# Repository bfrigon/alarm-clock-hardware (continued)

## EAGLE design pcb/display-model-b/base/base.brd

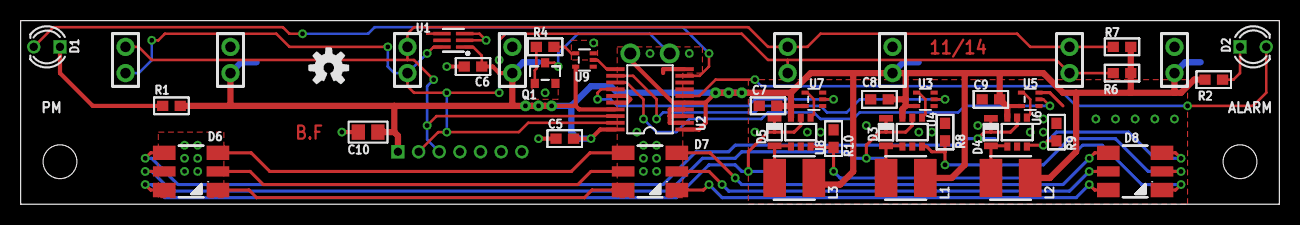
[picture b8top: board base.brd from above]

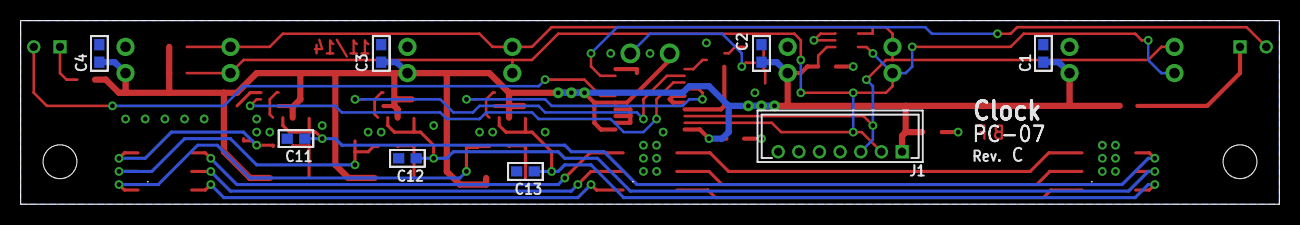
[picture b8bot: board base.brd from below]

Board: 2 copper layers, 121.9 x 17.8 mm, 52 parts (9 on the bottom side), 33 nets.

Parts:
C1, C2, C3, C4, C7, C8, C9, C11, C12, C13: 1uF; SMD_0603
C5, C6: 100nF; SMD_0603
C10: N/A; SMD_0805
D1, D2: {ATTR:COLOR}; LED_3MM
D3, D4, D5: SOD-323
D6, D7, D8: SMP6-RGB; LED_RGB_PLCC6
J1: SNG-2MM-HEADER-07-V; DF3X-7P-2DSA
L1, L2, L3: 22uH; IND-4X4
Q1: MMBT3904; SOT23
R1, R2: 82; SMD_0603
R4: 3k; SMD_0603
R6, R7: 1k; SMD_0603
R8, R9, R10: 5.1 (0.5%); SMD_0603
U1: TSL2561FN; DFN-6
U2: PCA9634PW; TSSOP20
U3, U5, U7, U9: 74AHC1G04DCK; SC70-5
U4, U6, U8: AP5724W; SOT23-6
U$1: INFO_DATE
U$3: OPENHW_LOGO_150
U$4: INFO_COMPACT
U$5: INFO_AUTHOR
X1, X2, X3, X4: CLOCK_LED_SEGMENT
X5: CLOCK_LED_DOTS

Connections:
3.3V: C1.2, C2.2, C3.2, C4.2, C5.1, C6.2, C7.2, C8.2, C9.2, C10.1, J1.1, L1.1, L2.1, L3.1, R1.2, R2.2, R6.2, R7.2, U1.1, U2.1, U2.5, U2.17, U2.20, U3.5, U4.6, U5.5, U6.6, U7.5, U8.6, U9.5, X1.VCC, X2.VCC, X3.VCC, X4.VCC, X5.VCC
DOTS: U2.11, U9.2
FB_B: D8.5, R10.2, U8.3
FB_G: D8.1, R9.2, U6.3
FB_R: D8.3, R8.2, U4.3
GND: C1.1, C2.1, C3.1, C4.1, C5.2, C6.1, C7.1, C8.1, C9.1, C10.2, C11.2, C12.2, C13.2, J1.4, Q1.2, R8.1, R9.1, R10.1, U1.2, U1.3, U2.2, U2.3, U2.4, U2.10, U2.15, U2.16, U3.3, U4.2, U5.3, U6.2, U7.3, U8.2, U9.3, X1.VSS, X2.VSS, X3.VSS, X4.VSS
unnamed: D6.3, D7.4
unnamed: D7.3, D8.4
unnamed: D7.1, D8.2
unnamed: D6.1, D7.2
unnamed: D6.5, D7.6
unnamed: D7.5, D8.6
unnamed: D3.A, L1.2, U4.1
unnamed: D4.A, L2.2, U6.1
unnamed: D5.A, L3.2, U8.1
unnamed: Q1.3, X5.VSS
unnamed: Q1.1, R4.2
unnamed: D2.K, U2.6
unnamed: D2.A, R2.1
unnamed: D1.A, R1.1
unnamed: D1.K, U2.9
unnamed: U3.4, U4.4
unnamed: R4.1, U9.4
unnamed: U5.4, U6.4
unnamed: U7.4, U8.4
PWM_B: U2.14, U7.2
PWM_G: U2.13, U5.2
PWM_R: U2.12, U3.2
SCL: J1.3, R7.1, U1.4, U2.18, X1.SCL, X2.SCL, X3.SCL, X4.SCL
SDA: J1.2, R6.1, U1.6, U2.19, X1.SDA, X2.SDA, X3.SDA, X4.SDA
SW_B: C13.1, D5.K, D6.6, U8.5
SW_G: C11.1, D4.K, D6.2, U6.5
SW_R: C12.1, D3.K, D6.4, U4.5

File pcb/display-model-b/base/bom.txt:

**********************************************************************************
*                                BILL OF MATERIAL                                *
**********************************************************************************

Last mod. : 2014-12-29 01:41:54
Doc. ID   : CLK-SCH-07
Project   : Alarm Clock (Model B)
Title     : Clock Display - Base
             
Part #    : CLK-PC-07
REV.      : C


Qty | Names              | Description                    | Mfg. SKU        | Package      | Value     
=======================================================================================================
  4 | U3, U5, U7, U9     | NOT Gate - Single              | 74AHC1G04DCK    | SC70-5       | --        
----|--------------------|--------------------------------|-----------------|--------------|-----------
  3 | U4, U6, U8         | White LED Step-up converter    | AP5724W         | SOT23-6      | --        
----|--------------------|--------------------------------|-----------------|--------------|-----------
  3 | D3-D5              | Schottky Diode - SMT 0603 -    | B0540WS         | SOD-323      | --        
----|--------------------|--------------------------------|-----------------|--------------|-----------
  2 | C5-C6              | Capacitor - SMT 0603 - 100nF   | CAP-0603        | SMT 0603     | 100nF     
----|--------------------|--------------------------------|-----------------|--------------|-----------
 10 | C1-C4, C7-C9,      | Capacitor - SMT 0603 - 1uF     | CAP-0603        | SMT 0603     | 1uF       
    | C11-C13            |                                |                 |              |           
----|--------------------|--------------------------------|-----------------|--------------|-----------
  1 | J1                 | 2mm Single Row Header - 7 pos  | DF3A-7P-2DSA    | DF3X-7P-2DSA | --        
    |                    | - SMT Vertical                 |                 |              |           
----|--------------------|--------------------------------|-----------------|--------------|-----------
  2 | D1-D2              | Led T1 (3mm) - Green           | LED-T1          | T1           | Green     
----|--------------------|--------------------------------|-----------------|--------------|-----------
  1 | Q1                 | NPN Transistor                 | MMBT3904        | SOT23        | --        
----|--------------------|--------------------------------|-----------------|--------------|-----------
  3 | L1-L3              | Inductor                       | NR4012T220M     | IND-4X4      | 22uH      
----|--------------------|--------------------------------|-----------------|--------------|-----------
  1 | U2                 | 8-bit fm+ i2c-bus LED driver   | PCA9634PW       | TSSOP20      | --        
----|--------------------|--------------------------------|-----------------|--------------|-----------
  2 | R6-R7              | Resistor - SMT 0603 - 1k       | RES-0603        | SMT 0603     | 1k        
----|--------------------|--------------------------------|-----------------|--------------|-----------
  1 | R4                 | Resistor - SMT 0603 - 3k       | RES-0603        | SMT 0603     | 3k        
----|--------------------|--------------------------------|-----------------|--------------|-----------
  3 | R8-R10             | Resistor - SMT 0603 - 5.1      | RES-0603        | SMT 0603     | 5.1       
    |                    | (0.5%)                         |                 |              | (0.5%)    
----|--------------------|--------------------------------|-----------------|--------------|-----------
  2 | R1-R2              | Resistor - SMT 0603 - 82       | RES-0603        | SMT 0603     | 82        
----|--------------------|--------------------------------|-----------------|--------------|-----------
  3 | D6-D8              | SMT RGB Led - PLCC6            | SMP6-RGB        | LED_RGB_PLCC | --        
    |                    |                                |                 | 6            |           
----|--------------------|--------------------------------|-----------------|--------------|-----------
  1 | U1                 | Light-to-digital converter     | TSL2561FN       | DFN-6        | --        
----|--------------------|--------------------------------|-----------------|--------------|-----------

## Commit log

2014-09-07 Added decoupling caps
2014-09-09 Cleaned up project tree
2014-09-18 Added Model B drawings
2014-10-19 Corrected drawings of touch panel PCB
2014-10-23 Overlay design
2014-10-28 Changed files for laser cutting to DXF instead of SVG
2014-12-29 Display base pcb (rev C), Touch panel (rev B)
2015-01-04 Changed page format on schematics to US letter (8.5" x 11")
2015-01-04 Moved notes to docs folder
2015-01-05 Updated mechanical drawings for model B
2015-01-06 3D render for model B
2015-01-06 BOM for audio test board
2015-01-07 Updated overlay to reflect the changes on touch pcb (rev B)
2015-01-09 Added marks for cutting
2015-01-09 Updated drawings to reflect changes on touch keypad PCB (leds on snooze, time and alarm button)
2015-01-22 at42qt1085 tests
2015-01-25 Added a temperature sensor IC (U9) to controller PCB
2015-01-25 Changed file format to .md for notes
2015-01-25 Corrected markdown syntax on notes
2015-01-29 Script to sets the correct title of each drawings and generate a TOC for the clk-dwg.pdf
2015-01-29 Updated design files
2015-02-08 Added battery interface PCB drawings (PC-08, DWG-12)
2015-02-08 modified dimensions of left panel PCB to fit speaker holder
2015-02-08 Modified fonts of title block on all drawings
2015-02-08 Added description to each Eagle project directories
2015-02-08 Created skeleton for PC-08 : Battery interface
2015-02-09 Fixed dimensions error in CLK-DWG-05 (Left panel PCB)
2015-02-11 Swapped USBC and USBB, USBC will be used for the PCM2704
2015-02-12 Fixed dimensions error in PC-04 (Left panel PCB)
2015-02-12 Switched motherboard (PC-03) to 4 layers design
2015-03-19 Converted motherboard and left-panel project files to Kicad
2015-03-21 Updated drawings for clk-pc-03
2015-04-06 Changed crystal location for PCM2704
2015-04-06 Added worksheet for left-panel
2015-04-12 Added bill of material for CLK-PC-03
2015-04-12 Tidy up motherboard schematic
2015-04-12 Added BOM for CLK-PC-04
2015-04-12 Updated schematic for CLK-PC-04
2015-04-12 Added components count on CLK-PC-03 BOM
2015-04-12 Added 3D views of PC-03 and PC04
2015-04-12 Create README.md file for CLK-PC-03
2015-04-12 Fixed incorrect sheet size for CLK-SCH-03 (Motherboard)
2015-04-12 Add gerber files
2015-04-12 Add README.md for PC-04
2015-04-12 Added gerber files for PC-04 (Left panel)
2015-04-12 Converted PC-08 (Battery interface) project files to Kicad
2015-04-12 Updated drawing for PC-08 (Battery interface)
2015-04-14 Added Debug connector in drawings
2015-04-14 Fixed wrong cap value for C24 and part # for C7,C9
2015-04-22 Incresed height of display epoxy casting by 1/16 inch
2015-04-22 Only modify pdf metadata for files that were modified
2015-05-03 Wrong polarity on battery connector label
